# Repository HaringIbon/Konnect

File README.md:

<div align="center">

# Konnect has moved to Konnect-EDA

## [Go to Konnect-EDA →](https://github.com/Orchis-ai-LLC/Konnect-EDA)

</div>

This repository is being archived, which makes it read-only. Development continues
at Konnect-EDA, from Orchis.ai LLC.

## It stays free, unless you're a business

Konnect-EDA is now commercial and closed source. Here's what that means for you:

- **Everyone, businesses included:** free until version 1.0.
- **Personal, hobby, student and open-hardware work:** still free after 1.0. You'll
  need a license key, and that key is free too.
- **Businesses:** a paid license from 1.0.

Business licenses pay for the work, and that's what lets us keep it free for
everyone else.

**Nothing here is being taken away.** The code and releases in this repository stay
available under the AGPL-3.0. The original
[KiCAD MCP Server](https://github.com/mixelpixx/KiCAD-MCP-Server) stays open source
under the MIT license and is still maintained. The boards you design are always yours.

## Where to go now

- **Downloads:** the [Konnect-EDA releases page](https://github.com/Orchis-ai-LLC/Konnect-EDA/releases).
  The first release is coming soon.
- **Bugs and feature requests:** the
  [Konnect-EDA issue tracker](https://github.com/Orchis-ai-LLC/Konnect-EDA/issues).
- **Want to help build it?** [Sign up to contribute](https://orchis.ai/konnect/join).
- **Contributed to Konnect?** Please [complete your sign-off](https://orchis.ai/konnect/sign-off)
  by November 20.
- **Using it at a company?** See [licensing](https://konnect-eda.orchis.ai/licensing/).

Thank you to everyone who built Konnect with us.

---

**AI-assisted PCB design for KiCAD 10.** Konnect is a native KiCAD plugin — a single
Rust binary — that lets Claude and other AI assistants design schematics and PCBs
through the [Model Context Protocol](https://modelcontextprotocol.io) (MCP).

**249 tools across 22 on-demand toolsets.** Schematic capture, PCB layout and
routing, ERC/DRC, design-review audits, JLCPCB part search, reference
circuits, and a full manufacturing export pipeline — with bundled skills and agents
that teach Claude KiCAD conventions out of the box.

## Why Konnect exists

Konnect is the successor to [KiCAD-MCP-Server](https://github.com/mixelpixx/KiCAD-MCP-Server),
a Python/TypeScript project that proved AI-driven PCB design works — and, in the
process, showed exactly where that architecture runs out of road. Konnect was built
to fix those specific problems:

**The call path was too long.** In the original server, a single tool call travels
through TypeScript, schema validation, a spawned Python subprocess, JSON over
stdin/stdout, a command router, and finally SWIG-generated C++ proxy objects before
anything touches your board. That's four language and serialization boundaries, each
with its own failure modes — subprocess lifecycle management, stdout parsing that
filters out warnings KiCAD leaks into the stream, chunked-JSON reassembly. In
Konnect, a tool call is a function call. One process, one language, no plumbing.

**The dependency surface was enormous.** Running the original means carrying Node.js
and its npm tree, Python and its pip packages, wxPython, kicad-skip, and KiCAD's
SWIG bindings — two package ecosystems plus a binding layer, every one of them a
moving target that can break an install. Konnect is a single static binary —
20–25 MB depending on platform, a ~9 MB download. There is nothing to install
alongside it and nothing to version-match.

**SWIG is a dead end.** The original's PCB backend depends on KiCAD's SWIG Python
bindings, which KiCAD is deprecating in favor of its IPC API. SWIG also carried
real operational scars: a zone-fill call that can segfault the backend, proxy-object
comparison bugs, and a fallback path that can silently swap backends mid-session.
Konnect talks to KiCAD 10 through the official IPC API (protobuf over NNG) — the
interface KiCAD is investing in — with real-time board edits that integrate with
KiCAD's own undo/redo.

**Schematic edits should not corrupt files.** Konnect edits `.kicad_sch` files
through its own S-expression engine with atomic writes (write, fsync, rename), UUID
preservation, and round-trip tests — no third-party schematic library with known
gaps, no text-manipulation workarounds.

**Context economy is a feature.** Exposing all 249 tools to an LLM costs roughly 23K
tokens of context on every listing. Konnect's router loads a starter kit (~2K
tokens) and lets the model pull in toolsets on demand — plus built-in observability
(`get_recent_calls`, `server_stats`, JSONL call logs) so the model can diagnose its
own tool failures.

The result is smaller, faster to install, aligned with where KiCAD is going, and
built for production use rather than experimentation. The original project remains
open, maintained, and useful — see [the comparison below](#relationship-to-kicad-mcp-server).

## What it does

Instead of describing changes and applying them by hand, the AI works your project
directly:

- **Place and wire schematic components** — add resistors, ICs, connectors; wire them
  together by pin name
- **Lay out the PCB** — place, move, rotate, and route footprints in real time via
  KiCAD's IPC API, with full undo/redo integration
- **Run design checks** — ERC, DRC, connectivity validation, decoupling audits,
  power-rail review, BOM health checks
- **Export production files** — Gerbers, drill, BOM, pick-and-place, 3D models, PDF
- **Search JLCPCB parts** — find in-stock components in a local 2.5M-part catalog and
  suggest alternatives
- **Start from reference circuits** — USB-C, LDO, buck converter, STM32, I2C, LED
  templates with verified component values
- **Watch it happen** — a live schematic viewer auto-refreshes as the AI edits

The full tool catalog is documented in [tool-directory.md](tool-directory.md).

## How it works

| Layer | Mechanism |
|-------|-----------|
| Schematic editing | Direct `.kicad_sch` S-expression editing with atomic writes (no KiCAD required) |
| PCB editing | KiCad 10 IPC API (NNG + protobuf) — real-time and undo-aware; single-footprint placement has a safe headless fallback |
| Specctra routing | Revision-bound Rust DSN export, local Freerouting MCP routing, and strict one-transaction SES import; an authenticated KiCad 10 native-export bridge is explicit opt-in |
| Exports & checks | `kicad-cli` subprocess (Gerber, PDF, ERC, DRC, …) |
| Transport | MCP JSON-RPC over stdio (default), or Streamable HTTP (`transport = "http"` / `"both"`) |

Explore the request path and safety boundaries in the
[interactive architecture diagrams](docs/ARCHITECTURE_DIAGRAMS.md). They are
published from a standalone documentation repository and add no dependencies to
Konnect.

## Installation

### From the KiCAD Plugin Manager (recommended)

1. Download the package for your OS from [Releases](https://github.com/mixelpixx/Konnect/releases):
   `konnect-pcm-v<version>-windows.zip`, `-macos.zip`, or `-linux.zip`. Each
   bundles that platform's server binary — the macOS package is a universal
   build, so one download covers Apple Silicon and Intel. (The `konnect-pcm-*`
   assets are the KiCAD plugin packages; the other archives are standalone
   server binaries.)
2. Open KiCAD 10 → **Plugin and Content Manager**
3. Click **Install from File** and select the zip
4. Restart KiCAD

Verify: open the **PCB Editor** → **Tools → External Plugins** → you should see
**Konnect**.

For KiCad 10, the Konnect settings dialog also offers an optional **native
Specctra bridge**. When enabled, `export_specctra_dsn` can ask the active PCB
Editor to generate its native DSN while Konnect still binds the export to the
exact IPC snapshot and creates the strict reverse manifest used during SES
import. The bridge is local-only, authenticated, disabled by default, and not
the KiCad 11 integration path. Konnect uses its Rust exporter by default;
`native_bridge_mode: "prefer"` enables fallback to Rust when the bridge is
unavailable, while `"require"` refuses instead.

For end-to-end autorouting, run `check_freerouting`, then
`export_specctra_dsn` → `route_specctra_dsn` →
`plan_specctra_ses_import` / `apply_specctra_ses`. Readiness reports engine
discovery, native-MCP compatibility, and complete bridge availability
separately. The owned Java child is loopback-only and is reaped on success,
failure, timeout, or cancellation. The first supported profile preserves fixed
straight tracks and through vias; unlocked routing, arcs, zones, and unsupported
geometry are rejected before mutation.

### Build from source

```bash
# protoc is required (protobuf code generation), and cmake (the nng crate
# compiles the NNG C library with it).
# Windows: choco install protoc cmake
# macOS:   brew install protobuf cmake
# Linux:   apt install protobuf-compiler cmake
cargo build --release -p konnect
```

### Install guidance for your AI client

Konnect bundles shared KiCad skills for Claude and Codex. Select the client when
installing, checking, or removing that guidance:

```bash
# Existing behavior remains the default: Claude skills, agents, and hooks
konnect init

# Codex installs only the shared skills under ~/.agents/skills
konnect init --client codex
konnect status --client codex
konnect uninstall --client codex
```

MCP server startup never installs or restores guidance. Run `konnect init`
explicitly when you want those files installed; after `konnect uninstall`,
starting the server leaves them removed.

Guidance written by an older `konnect init` is not updated by upgrading the
binary. `konnect status` compares every installed skill, agent, and hook with
the bundle in the binary you run and marks each `current`, `different`, or
`missing`. The server makes the same check once for each installed version:
the first start after `konnect init` compares the files, records
the result in `~/.konnect`, and adds a one-line notice to its `initialize`
instructions if guidance is out of sync. Later starts reuse that record, so
guidance you chose to keep is not reported again. `get_installation_info`
shows the result. Re-run `konnect init` to update it.
It overwrites differing files, so keep a copy of any file you edited. `--client` remains accepted in server
commands for compatibility. For example, register a standalone binary with the
Codex CLI using:

```bash
codex mcp add konnect -- /path/to/konnect --client codex
```

Claude remains the default when `--client` is omitted. The installer tracks the
two clients independently, and a Codex install does not create or modify
`~/.claude`.

`--help` on any subcommand prints that subcommand's usage and writes nothing —
`konnect init --help` describes the installer rather than running it. An
argument Konnect does not recognise is an error rather than being ignored, so a
typo such as `--cleint codex` stops instead of quietly installing for the
default client.

To verify which Konnect process an MCP client is actually using, call the
always-visible `get_installation_info` tool. It reports the serving build,
executable path, verified installation source when one can be proven, KiCad
CLI and IPC detection, and restart guidance. A missing build commit or an
`unknown` installation source means the available evidence was insufficient;
it is not silently guessed from a directory name.

### macOS

The [Releases](https://github.com/mixelpixx/Konnect/releases) page ships
standalone server binaries for both Apple Silicon (`aarch64-apple-darwin`) and
Intel (`x86_64-apple-darwin`). They are not yet code-signed, so if you download
one through a browser, clear the quarantine flag before first launch:

```bash
tar xzf konnect-v*-aarch64-apple-darwin.tar.gz
xattr -d com.apple.quarantine ./konnect   # only needed for browser downloads
./konnect --help
```

Or build from source as above (verified on Apple Silicon; the same
`target/release/konnect` binary is the MCP server).

KiCad on macOS keeps its tools inside the app bundle and they are not on
`PATH`, so point Konnect at them in `~/Library/Application Support/konnect/config.toml`:

```toml
kicad_cli = "/Applications/KiCad/KiCad.app/Contents/MacOS/kicad-cli"
kicad_binary = "/Applications/KiCad/KiCad.app/Contents/MacOS/kicad"
# KiCad 10's IPC socket on macOS (enable it in KiCad:
# Preferences → Plugins → "Enable KiCad API")
ipc_address = "ipc:///tmp/kicad/api.sock"
```

Claude Desktop's config lives at
`~/Library/Application Support/Claude/claude_desktop_config.json`:

```json
{
  "mcpServers": {
    "konnect": {
      "command": "/path/to/konnect"
    }
  }
}
```

For Claude Code, put the same snippet in a `.mcp.json` in your project root.

The macOS PCM package (`konnect-pcm-v<version>-macos.zip`) bundles a universal
server binary, so one download covers Apple Silicon and Intel. The schematic
viewer compiles and launches on macOS (Tauri 2 uses the system WKWebView —
WebView2 is only a Windows requirement) but hasn't had the same mileage as
the Windows build yet.

## Setup with Claude Desktop

After a PCM install, the server binary lives in your KiCAD documents folder:

```
C:\Users\<YOU>\Documents\KiCad\10.0\3rdparty\plugins\com_github_mixelpixx_konnect\bin\konnect.exe
```

Edit `%APPDATA%\Claude\claude_desktop_config.json`:

```json
{
  "mcpServers": {
    "konnect": {
      "command": "C:\\Users\\<YOU>\\Documents\\KiCad\\10.0\\3rdparty\\plugins\\com_github_mixelpixx_konnect\\bin\\konnect.exe"
    }
  }
}
```

Restart Claude Desktop and the Konnect tools appear. For Claude Code, drop the same
snippet into a `.mcp.json` in your project root (see [examples/](examples/)).

## Schematic viewer

A standalone viewer that auto-refreshes as the schematic file changes:

```bash
schematic-viewer.exe path\to\your\root_schematic.kicad_sch
```

Point it at the root sheet of a hierarchical design and every sub-sheet is rendered
too, with a depth-indented sheet selector in the toolbar. Edits saved from KiCAD (or
made by the AI through the schematic tools) re-render only the sheets that changed
and refresh the view live — rendering runs against temp-folder snapshots, so the
viewer never blocks KiCAD from saving. Pan with click-drag, zoom with the wheel,
`0` to fit, `R` to refresh, drag-and-drop to open a different file. Also launchable
by the AI via the `open_schematic_viewer` tool.

Needs the WebView2 runtime (pre-installed on Windows 10/11) and a KiCAD install for
`kicad-cli` (auto-discovered, or pass `--kicad-cli <path>`). Built separately from
the main workspace — see [DEV.md](DEV.md) for build steps.

## Requirements

- KiCAD 10 (Windows is the most-tested platform; macOS works from the release
  binaries or a source build — see the [macOS section](#macos) above. Linux
  compiles and passes tests in CI but hasn't had per-platform QA yet; both are
  tracked on the [roadmap](ROADMAP.md))
- `kicad-cli` (ships with KiCAD — used for exports, ERC, DRC)
- For most PCB tools: KiCAD running with the target board open (IPC API).
  `place_component`, `move_component`, `rotate_component`, and (on KiCAD
  10.0.6+) `flip_component` can safely fall back to a closed board file when
  IPC is unreachable. An older reachable KiCAD makes `flip_component` fail
  closed with `unsupported_capability`; it never edits the file underneath a
  live editor that cannot perform the native flip.

## License: free for the little guys

Konnect is licensed under the **[GNU AGPL-3.0](LICENSE)**.

If you're a hobbyist, student, freelancer, or open-source project: **use it freely,
no strings attached.** Design boards, ship them, sell them.

If you're a business: the AGPL requires that anything you build on or around Konnect —
including software provided over a network — be open-sourced under the same license.
If that doesn't work for you, **commercial licenses are available**: see
[COMMERCIAL.md](COMMERCIAL.md).

## Relationship to KiCAD-MCP-Server

The original [Python/TypeScript project](https://github.com/mixelpixx/KiCAD-MCP-Server)
remains fully open (MIT) and maintained. Konnect is where new development happens —
the architecture it proved, rebuilt for production:

| | KiCAD-MCP-Server | Konnect |
|---|---|---|
| Runtime | Node.js + Python + SWIG bindings | Single static binary (20–25 MB) |
| Tool call path | TS → subprocess → Python → SWIG C++ | Direct function call |
| PCB backend | SWIG (deprecated by KiCAD) + experimental IPC | KiCAD 10 IPC API |
| Schematic backend | kicad-skip + custom loaders | Native S-expression engine, atomic writes |
| Context cost | Router pattern | Load/unload toolsets + observability |
| Skills / agents | — | 6 skills + 2 agents bundled |
| License | MIT | AGPL-3.0 + commercial |

## Troubleshooting

**Plugin doesn't appear in KiCAD** — install via the Plugin and Content Manager (not
manual copy), then restart KiCAD.

**PCB tools return "KiCAD must be running with the board loaded"** — open KiCAD
with that board first; most PCB tools talk to the running PCB editor. Only an
unreachable KiCAD produces that message: if KiCAD is running and the tool
refuses anyway, the error is the tool's own reason for refusing.
`place_component`, `move_component`, `rotate_component`, and (on KiCAD
10.0.6+) `flip_component` can fall back to a closed board file when no KiCAD
process is reachable. An older, reachable KiCAD makes `flip_component` refuse
rather than silently editing the file underneath it.

See [docs/TROUBLESHOOTING.md](docs/TROUBLESHOOTING.md) for socket setup, tools
that don't appear after `load_toolset`, and transaction recovery.

**"kicad-cli not found"** — common install paths are auto-detected; set the path
explicitly in the plugin settings dialog, in a `settings.json` beside the binary,
or in a `konnect.toml` in the working directory. (A file under any other name
works only when passed with `--config`.)

## Support

- Community Discord: [join the Konnect community](https://discord.gg/NVp9RGMmDu)
  for installation help, AI-client setup, design-workflow discussion,
  contributor coordination, and live project-status updates
- Issues & feature requests: [GitHub Issues](https://github.com/mixelpixx/Konnect/issues)
- Roadmap: [ROADMAP.md](ROADMAP.md)
- Contributing: [CONTRIBUTING.md](CONTRIBUTING.md)

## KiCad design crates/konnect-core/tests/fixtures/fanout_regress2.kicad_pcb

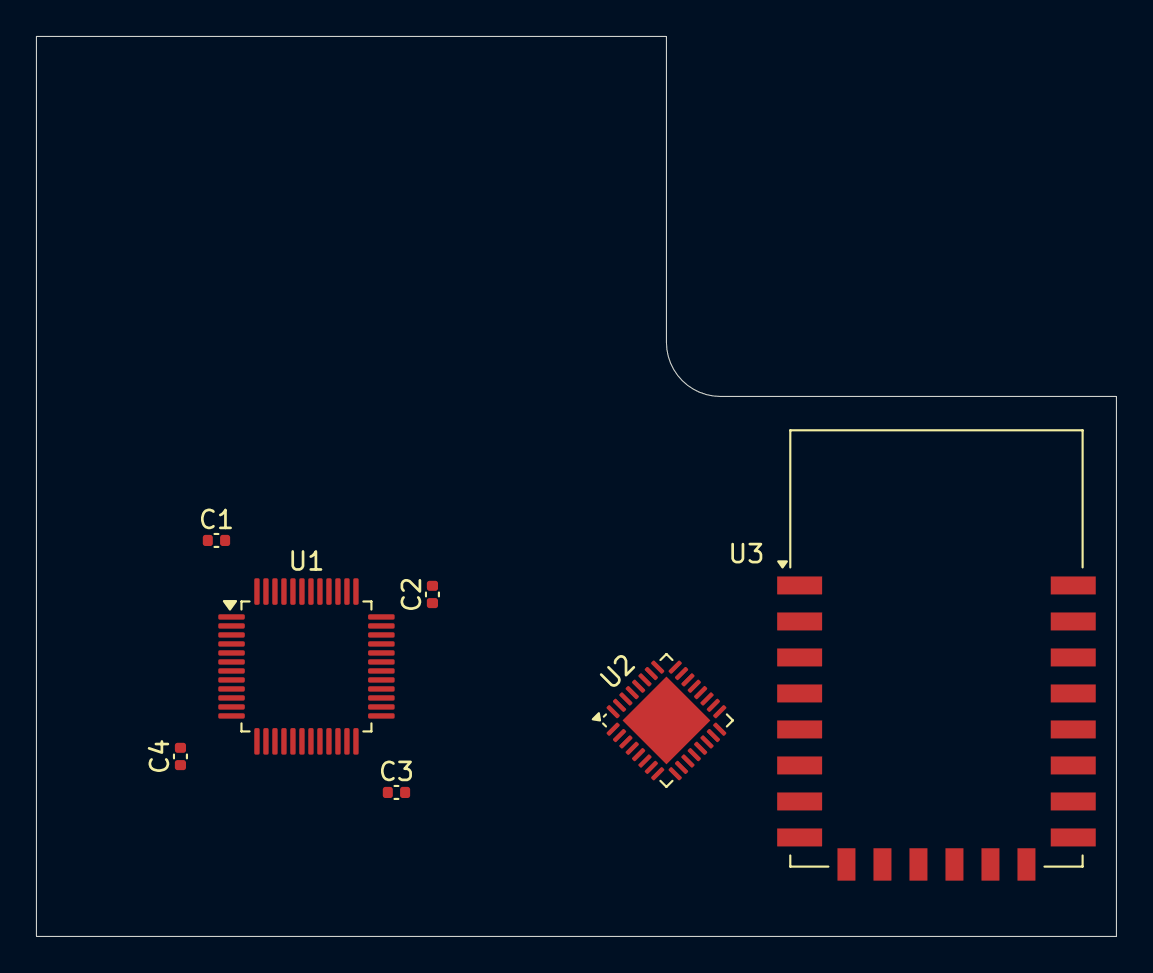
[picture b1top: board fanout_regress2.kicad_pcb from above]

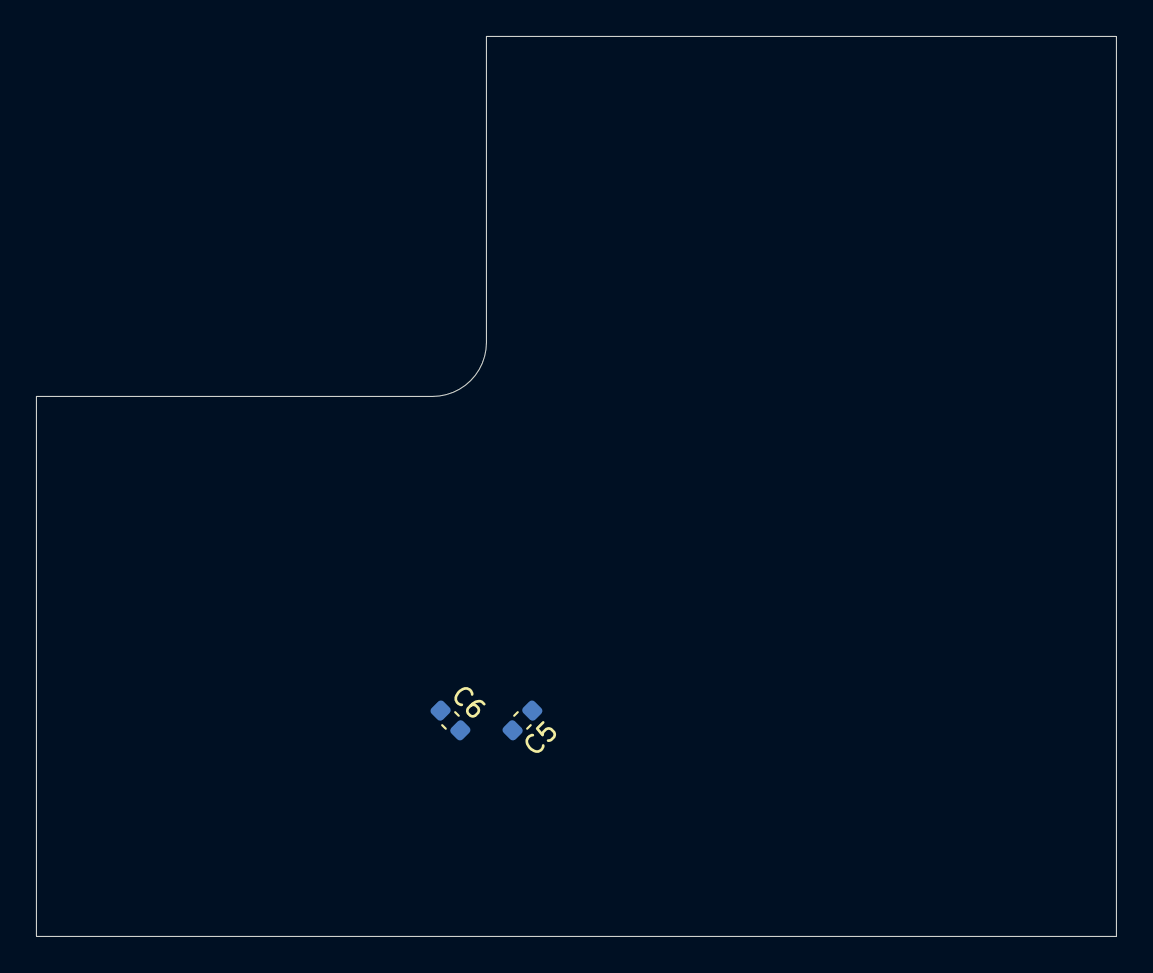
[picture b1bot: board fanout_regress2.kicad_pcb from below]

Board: 4 copper layers, 60.0 x 50.0 mm, 9 parts (2 on the bottom side), 10 nets, no tracks yet.

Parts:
C1, C2, C3, C4: C_0402_1005Metric
C5, C6: C_0603_1608Metric
U1: LQFP-48_7x7mm_P0.5mm
U2: QFN-32-1EP_5x5mm_P0.5mm_EP3.45x3.45mm
U3: ESP-12E

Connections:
+3V3: C1.1, C2.1, C3.1, C4.1, C5.1, C6.1, U1.1, U1.9, U1.24, U1.36, U1.48, U2.4, U2.12, U2.20, U3.8
GND: C1.2, C2.2, C3.2, C4.2, C5.2, C6.2, U1.8, U1.23, U1.35, U1.47, U2.5, U2.13, U2.33, U3.15
SIG0: U1.10, U2.25
SIG1: U1.11, U2.26
SIG2: U1.12, U2.27
SIG3: U1.13, U2.28
SIG4: U1.14, U2.29
SIG5: U1.15, U2.30
SIG6: U1.16, U2.31
SIG7: U1.17, U2.32

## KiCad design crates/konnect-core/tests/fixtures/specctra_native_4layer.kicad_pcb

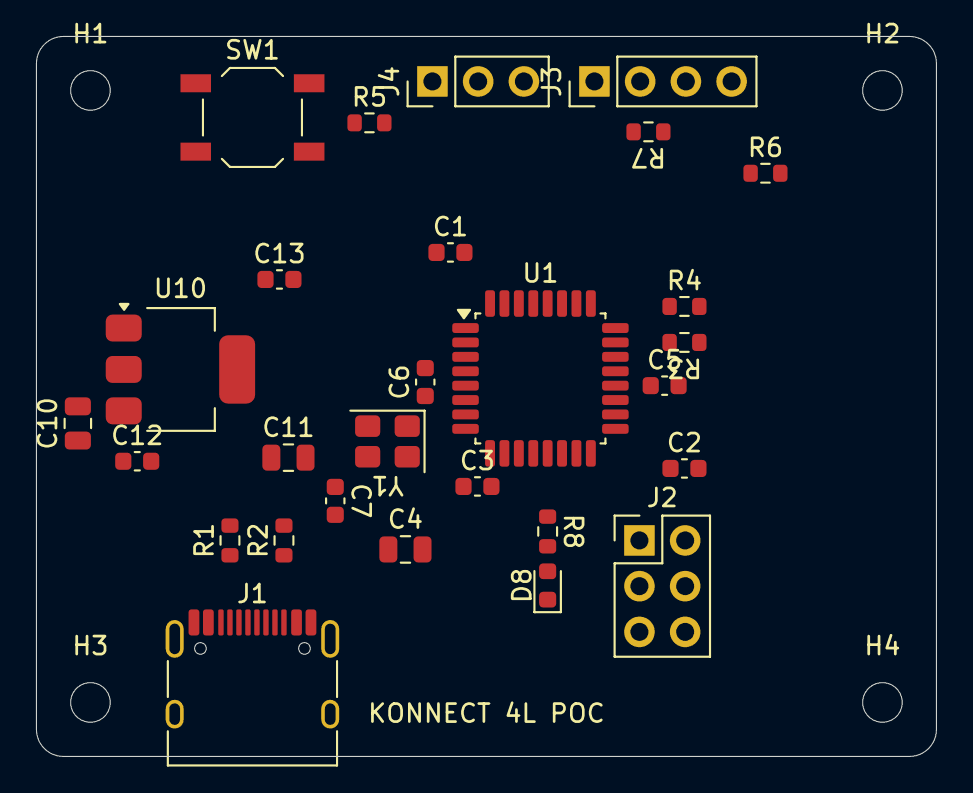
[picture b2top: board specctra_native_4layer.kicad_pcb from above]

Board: 4 copper layers, 50.0 x 40.0 mm, 32 parts (0 on the bottom side), 19 nets, no tracks yet.

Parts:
C1, C2, C3, C5, C12, C13: 100nF; C_0603_1608Metric
C4, C10, C11: 10uF; C_0805_2012Metric
C6, C7: 22pF; C_0603_1608Metric
D8: RED; LED_0603_1608Metric
H1, H2, H3, H4: MountingHole_2.2mm_M2
J1: USB_C; USB_C_Receptacle_HRO_TYPE-C-31-M-12
J2: ISP; PinHeader_2x03_P2.54mm_Vertical
J3: I2C; PinHeader_1x04_P2.54mm_Vertical
J4: UART; PinHeader_1x03_P2.54mm_Vertical
R1, R2: 5.1k; R_0603_1608Metric
R3, R4, R5: 10k; R_0603_1608Metric
R6, R7: 4.7k; R_0603_1608Metric
R8: 680; R_0603_1608Metric
SW1: RESET; SW_SPST_TL3342
U1: ATmega328P-AU; TQFP-32_7x7mm_P0.8mm
U10: AMS1117-3.3; SOT-223-3_TabPin2
Y1: 8MHz; Crystal_SMD_3225-4Pin_3.2x2.5mm

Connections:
+3V3: C1.1, C2.1, C3.1, C4.1, C11.1, C13.1, J2.2, J3.1, R5.1, R6.2, R7.2, U1.4, U1.6, U1.18, U10.2
+5V: C10.1, C12.1, J1.A4, J1.A9, J1.B4, J1.B9, R3.1, U10.3
/AREF: C5.1, U1.20
/LED_A: D8.2, R8.2
/LED_DRV: R8.1, U1.13
/MISO: J2.1, U1.16
/MOSI: J2.4, U1.15
/Power/CC1: J1.A5, R1.1
/Power/CC2: J1.B5, R2.1
/RESET: J2.5, R5.2, SW1.1, U1.29
/RXD: J4.3, U1.30
/SCK: J2.3, U1.17
/SCL: J3.3, R7.1, U1.28
/SDA: J3.4, R6.1, U1.27
/TXD: J4.2, U1.31
/VBUS_SENSE: R3.2, R4.1, U1.23
/XTAL1: C6.1, U1.7, Y1.1
/XTAL2: C7.1, U1.8, Y1.3
GND: C1.2, C2.2, C3.2, C4.2, C5.2, C6.2, C7.2, C10.2, C11.2, C12.2, C13.2, D8.1, J1.A1, J1.A12, J1.B1, J1.B12, J1.SH, J2.6, J3.2, J4.1, R1.2, R2.2, R4.2, SW1.2, U1.3, U1.5, U1.21, U10.1, Y1.2, Y1.4
